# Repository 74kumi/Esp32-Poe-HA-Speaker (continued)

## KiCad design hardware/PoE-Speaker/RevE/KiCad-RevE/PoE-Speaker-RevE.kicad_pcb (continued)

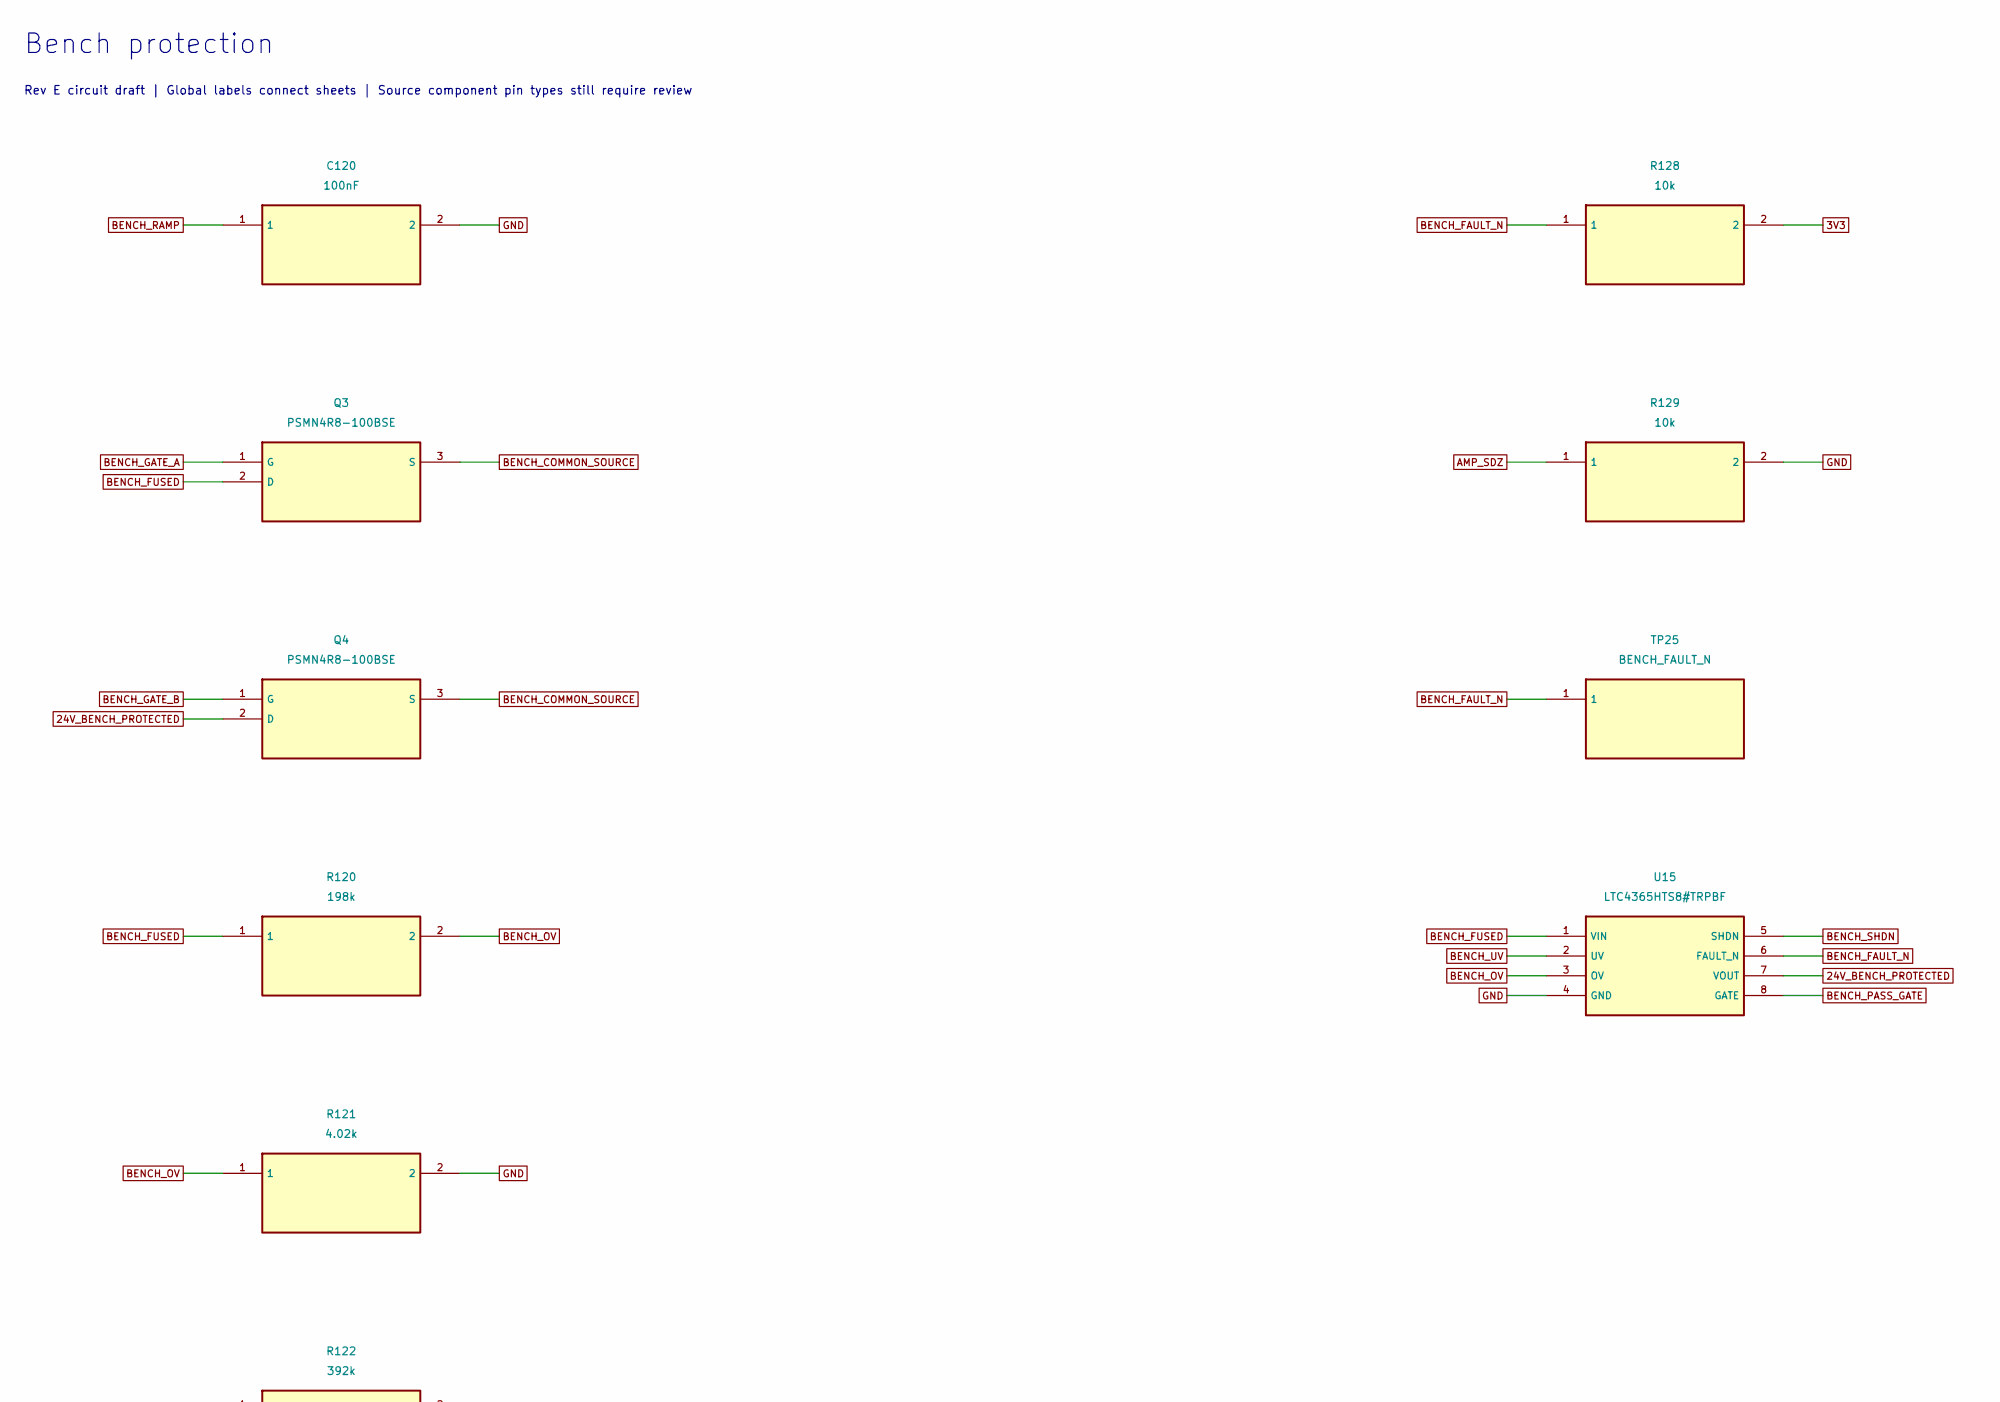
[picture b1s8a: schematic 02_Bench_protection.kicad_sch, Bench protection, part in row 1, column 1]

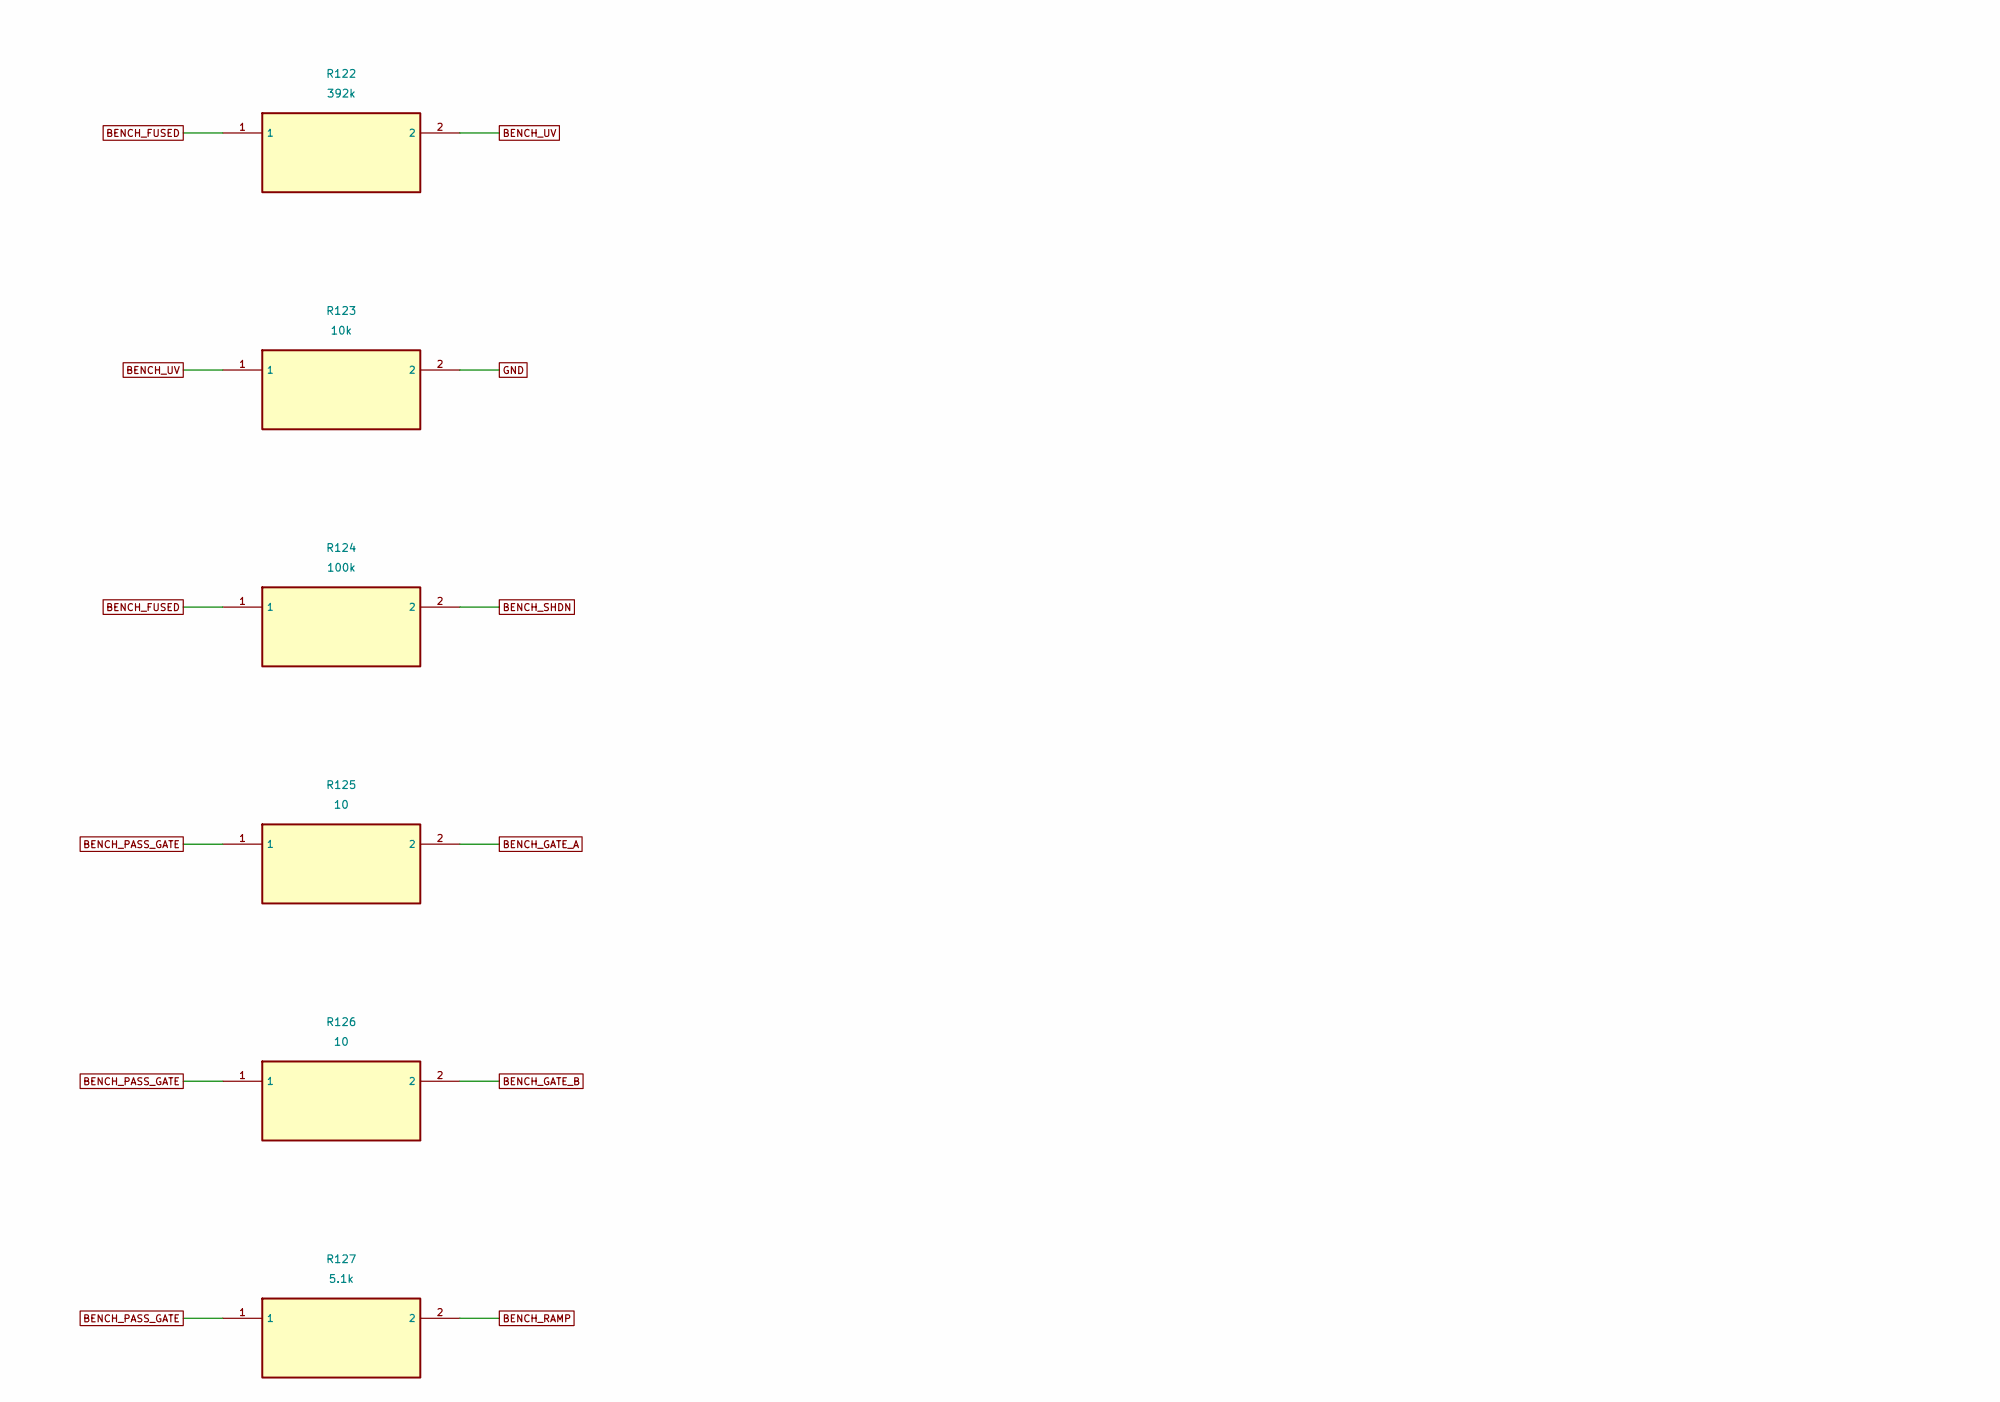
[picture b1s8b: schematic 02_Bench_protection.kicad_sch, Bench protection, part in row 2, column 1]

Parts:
C120: 100nF; C_1210_3225Metric; Voltage Rating 100 V; Tolerance 5%; Manufacturer Part Number C1210C104J1GACTU
Q3: PSMN4R8-100BSE; Q3_RevB; Manufacturer Part Number PSMN4R8-100BSE
Q4: PSMN4R8-100BSE; Q4_RevB; Manufacturer Part Number PSMN4R8-100BSE
R120: 198k; R120_RevB; Tolerance 0.1%; Power rating 0.125 W conservative; Manufacturer Part Number TNPW0805198KBYEA
R121: 4.02k; R121_RevB; Tolerance 0.1%; Power rating 0.125 W conservative; Manufacturer Part Number TNPW08054K02BYEA
R122: 392k; R122_RevB; Tolerance 1%; Power rating 0.125 W conservative; Manufacturer Part Number TNPW0805392KFHEA
R123: 10k; R123_RevB; Tolerance 1%; Power rating 0.125 W conservative; Manufacturer Part Number TNPW080510K0FHEA
R124: 100k; R124_RevB; Tolerance 1%; Power rating 0.125 W conservative; Manufacturer Part Number TNPW0805100KFHEA
R125: 10; R125_RevB; Tolerance 1%; Power rating 0.125 W conservative; Manufacturer Part Number TNPW080510R0FHEA
R126: 10; R126_RevB; Tolerance 1%; Power rating 0.125 W conservative; Manufacturer Part Number TNPW080510R0FHEA
R127: 5.1k; R127_RevB; Tolerance 1%; Power rating 0.125 W conservative; Manufacturer Part Number TNPW08055K10FHEA
R128: 10k; R128_RevB; Tolerance 1%; Power rating 0.125 W conservative; Manufacturer Part Number TNPW080510K0FHEA
R129: 10k; R129_RevB; Tolerance 1%; Power rating 0.125 W conservative; Manufacturer Part Number TNPW080510K0FHEA
TP25: BENCH_FAULT_N; TP25_RevB; Manufacturer Part Number BENCH_FAULT_N
U15: LTC4365HTS8#TRPBF; U15_RevB; Manufacturer Part Number LTC4365HTS8#TRPBF

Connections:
3V3: R128.2; also elsewhere on the board
24V_BENCH_PROTECTED: Q4.2 (D), U15.7 (VOUT); also elsewhere on the board
AMP_SDZ: R129.1; also elsewhere on the board
BENCH_COMMON_SOURCE: Q3.3 (S), Q4.3 (S)
BENCH_FAULT_N: R128.1, TP25.1, U15.6 (FAULT_N)
BENCH_FUSED: Q3.2 (D), R120.1, R122.1, R124.1, U15.1 (VIN); also elsewhere on the board
BENCH_GATE_A: Q3.1 (G), R125.2
BENCH_GATE_B: Q4.1 (G), R126.2
BENCH_OV: R120.2, R121.1, U15.3 (OV)
BENCH_PASS_GATE: R125.1, R126.1, R127.1, U15.8 (GATE)
BENCH_RAMP: C120.1, R127.2
BENCH_SHDN: R124.2, U15.5 (SHDN)
BENCH_UV: R122.2, R123.1, U15.2 (UV)
GND: C120.2, R121.2, R123.2, R129.2, U15.4 (GND); also elsewhere on the board

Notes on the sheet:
Bench protection
Rev E circuit draft | Global labels connect sheets | Source component pin types still require review

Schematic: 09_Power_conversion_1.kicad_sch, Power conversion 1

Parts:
C3: 1000uF; C3_RevB; Voltage Rating 35V; Manufacturer Part Number EEUFR1V102
C4: 1000uF; C4_RevB; Voltage Rating 35V; Manufacturer Part Number EEUFR1V102
C40: 10uF; C40_RevB; Voltage Rating 50 V; Tolerance 10%; Manufacturer Part Number C1210C106K5RACTU
C41: 220nF; C41_RevB; Voltage Rating 50 V; Tolerance 10%; Manufacturer Part Number C0603C224K5RACTU
C42: 100nF; C42_RevB; Voltage Rating 50 V; Tolerance 10%; Manufacturer Part Number C0603C104K5RACTU
C43: 1uF; C43_RevB; Voltage Rating 16 V; Tolerance 10%; Manufacturer Part Number C0603C105K4RACTU
C44: 22uF; C44_RevB; Voltage Rating 25 V; Tolerance 10%; Manufacturer Part Number C1210C226K3RACTU
C45: 22uF; C45_RevB; Voltage Rating 25 V; Tolerance 10%; Manufacturer Part Number C1210C226K3RACTU
C46: 22uF; C46_RevB; Voltage Rating 25 V; Tolerance 10%; Manufacturer Part Number C1210C226K3RACTU
C47: 22uF; C47_RevB; Voltage Rating 25 V; Tolerance 10%; Manufacturer Part Number C1210C226K3RACTU
C48: 10uF; C48_RevB; Voltage Rating 16 V; Tolerance 10%; Manufacturer Part Number GRM21BR61C106KE15L
C49: 22uF; C49_RevB; Voltage Rating 16 V; Tolerance 20%; Manufacturer Part Number GRM21BR61C226ME44L
C50: 47uF; C50_RevB; Voltage Rating 16 V; Tolerance 10%; Manufacturer Part Number GRM32ER61C476KE15L
C53: 3.3nF; C53_RevB; Voltage Rating 50 V; Tolerance 5%; Manufacturer Part Number C0603C332J5GACTU
D11: SMBJ26CA; D11_RevB; Manufacturer Part Number SMBJ26CA
F1: 24T 3.15A250V; F1_RevB; Manufacturer Part Number 24T 3.15A250V; LCSC Part Number C2905508
J2: MX2EDGR-5.08-02P-GN01-Cu-A; J2_RevB; Manufacturer Part Number MX2EDGR-5.08-02P-GN01-Cu-A; LCSC Part Number C5187973
L3: 8.2uH; L3_RevB; Current Rating 4A; Part Type Inductor
L4: 2.2uH; L4_RevB; Current Rating 4A; Part Type Inductor
Q1: DMNH6012LK3-13; Q1_RevB; Manufacturer Part Number DMNH6012LK3-13
Q2: DMNH6012LK3-13; Q2_RevB; Manufacturer Part Number DMNH6012LK3-13

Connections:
3V3: C49.1, C50.1, L4.2; also elsewhere on the board
5V: C44.1, C45.1, C46.1, C47.1, C48.1, L3.2; also elsewhere on the board
24V_AMP: C3.1, C4.1, C40.1, C41.1; also elsewhere on the board
24V_BENCH_PROTECTED: Q2.3 (S); also elsewhere on the board
24V_BENCH_RAW: F1.1, J2.1; also elsewhere on the board
24V_OR: Q1.2 (D), Q2.2 (D); also elsewhere on the board
24V_POE: Q1.3 (S); also elsewhere on the board
BENCH_FUSED: D11.1 (K), F1.2; also elsewhere on the board
BENCH_OR_GATE: Q2.1 (G); also elsewhere on the board
BUCK3V3_SS: C53.1; also elsewhere on the board
BUCK3V3_SW: L4.1; also elsewhere on the board
BUCK5_BOOT: C42.1; also elsewhere on the board
BUCK5_SW: C42.2, L3.1; also elsewhere on the board
BUCK5_VCC: C43.1; also elsewhere on the board
GND: C3.2, C4.2, C40.2, C41.2, C43.2, C44.2, C45.2, C46.2, C47.2, C48.2, C49.2, C50.2, C53.2, D11.2 (A), J2.2; also elsewhere on the board
POE_OR_GATE: Q1.1 (G); also elsewhere on the board

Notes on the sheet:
Power conversion 1
Rev E circuit draft | Global labels connect sheets | Source component pin types still require review

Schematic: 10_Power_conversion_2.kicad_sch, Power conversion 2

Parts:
R23: 100kΩ; R23_RevB; Tolerance 1%; Power rating 0.10 W conservative; Part Type Resistor
R24: 24.9kΩ; R24_RevB; Tolerance 1%; Power rating 0.10 W conservative; Part Type Resistor
R35: 100kΩ; R35_RevB; Tolerance 1%; Power rating 0.10 W conservative; Part Type Resistor
R36: 100kΩ; R36_RevB; Tolerance 1%; Power rating 0.10 W conservative; Part Type Resistor
U6: LMR33630AQRNXRQ1; U6_RevB; Manufacturer Part Number LMR33630AQRNXRQ1
U7: TPS62132RGTR; U7_RevB; Part Type Integrated Circuit
U9: LM5050-2; U9_RevB; Manufacturer Part Number LM5050MK-2/NOPB
U10: LM5050-2; U10_RevB; Manufacturer Part Number LM5050MK-2/NOPB

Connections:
3V3: R36.2, U7.7 (FSW), U7.14 (VOS); also elsewhere on the board
3V3_PG: R36.1, U7.4 (PG); also elsewhere on the board
5V: R23.1, R35.2, U7.10 (AVIN), U7.11 (PVIN_1), U7.12 (PVIN_2), U7.13 (EN); also elsewhere on the board
5V_PG: R35.1, U6.8 (PG); also elsewhere on the board
24V_AMP: U6.2 (VIN), U6.9 (EN), U6.10 (VIN); also elsewhere on the board
24V_BENCH_PROTECTED: U10.4 (IN); also elsewhere on the board
24V_OR: U9.6 (OUT), U10.6 (OUT); also elsewhere on the board
24V_POE: U9.4 (IN); also elsewhere on the board
BENCH_OR_GATE: U10.5 (GATE); also elsewhere on the board
BUCK3V3_SS: U7.9 (SS/TR); also elsewhere on the board
BUCK3V3_SW: U7.1 (SW_1), U7.2 (SW_2), U7.3 (SW_3); also elsewhere on the board
BUCK5_BOOT: U6.4 (BST); also elsewhere on the board
BUCK5_FB: R23.2, R24.1, U6.7 (FB)
BUCK5_SW: U6.3 (NC), U6.12 (SW); also elsewhere on the board
BUCK5_VCC: U6.5 (VCC); also elsewhere on the board
GND: R24.2, U6.1 (PGND), U6.6 (AGND), U6.11 (PGND), U7.5 (FB), U7.6 (AGND), U7.8 (DEF), U7.15 (PGND_1), U7.16 (PGND_2), U7.17 (EP), U9.2 (GND), U9.3 (OFF), U10.2 (GND), U10.3 (OFF); also elsewhere on the board
POE_OR_GATE: U9.5 (GATE); also elsewhere on the board

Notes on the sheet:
Rev E circuit draft | Global labels connect sheets | Source component pin types still require review
Power conversion 2

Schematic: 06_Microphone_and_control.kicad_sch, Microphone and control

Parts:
C55: 100nF; C55_RevB; Voltage Rating 50 V; Tolerance 10%; Manufacturer Part Number C0603C104K5RACTU
C56: 100nF; C56_RevB; Voltage Rating 50 V; Tolerance 10%; Manufacturer Part Number C0603C104K5RACTU
C57: 100nF; C57_RevB; Voltage Rating 50 V; Tolerance 10%; Manufacturer Part Number C0603C104K5RACTU
J4: Pin Header 02x07 2.54mm Vertical; J4_RevB; Manufacturer Part Number TSW-107-07-G-D
J6: Pin Header 01x06 2.54mm Vertical; J6_RevB; Part Type Connector
R28: 33Ω; R28_RevB; Tolerance 1%; Power rating 0.10 W conservative; Part Type Resistor
R29: 33Ω; R29_RevB; Tolerance 1%; Power rating 0.10 W conservative; Part Type Resistor
R30: 33Ω; R30_RevB; Tolerance 1%; Power rating 0.10 W conservative; Part Type Resistor
R31: 33Ω; R31_RevB; Tolerance 1%; Power rating 0.10 W conservative; Part Type Resistor
R32: 33Ω; R32_RevB; Tolerance 1%; Power rating 0.10 W conservative; Part Type Resistor
R33: 4.7kΩ; R33_RevB; Tolerance 1%; Power rating 0.10 W conservative; Part Type Resistor
R34: 4.7kΩ; R34_RevB; Tolerance 1%; Power rating 0.10 W conservative; Part Type Resistor
R38: 10kΩ; R38_RevB; Tolerance 1%; Power rating 0.10 W conservative; Part Type Resistor
U11: PCAL6416APW; U11_RevB; Manufacturer Part Number PCAL6416APW

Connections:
3V3: C55.1, C56.1, C57.1, J4.1, J6.1, R33.1, R34.1, R38.1, U11.2 (VDD_I2C), U11.24 (VDD_P); also elsewhere on the board
3V3_PG: U11.14 (P1_1); also elsewhere on the board
5V_PG: U11.13 (P1_0); also elsewhere on the board
AMP_ENABLE_CMD: U11.4 (P0_0); also elsewhere on the board
AMP_FAULTZ: U11.8 (P0_4); also elsewhere on the board
AMP_MUTE: U11.5 (P0_1); also elsewhere on the board
DAC_XSMT: U11.6 (P0_2); also elsewhere on the board
EXP_GPIO0: J6.5, U11.15 (P1_2)
EXP_GPIO1: J6.6, U11.16 (P1_3)
GND: C55.2, C56.2, C57.2, J4.2, J4.4, J4.6, J4.8, J4.10, J6.2, U11.12 (VSS), U11.21 (ADDR); also elsewhere on the board
I2C_SCL: J4.13, J6.4, R34.2, U11.22 (SCL); also elsewhere on the board
I2C_SDA: J4.12, J6.3, R33.2, U11.23 (SDA); also elsewhere on the board
IOX_INT_N: U11.1 (~INT); also elsewhere on the board
IOX_nRESET: R38.2, U11.3 (~RESET); also elsewhere on the board
PDM_CLK: J4.3, R28.2; also elsewhere on the board
PDM_CLK_MCU: R28.1; also elsewhere on the board
PDM_DATA0: R29.2; also elsewhere on the board
PDM_DATA0_CONN: J4.5, R29.1
PDM_DATA1: R30.2; also elsewhere on the board
PDM_DATA1_CONN: J4.7, R30.1
PDM_DATA2: R31.2; also elsewhere on the board
PDM_DATA2_CONN: J4.9, R31.1
PDM_DATA3: R32.2; also elsewhere on the board
PDM_DATA3_CONN: J4.11, R32.1
PHY_nRESET: U11.7 (P0_3); also elsewhere on the board
POE_AT_DET: U11.9 (P0_5); also elsewhere on the board
POE_BT3_DET: U11.10 (P0_6); also elsewhere on the board
POE_BT4_DET: U11.11 (P0_7); also elsewhere on the board
RING_GPIO_SPARE: J4.14; also elsewhere on the board
STATUS_LED_K: U11.17 (P1_4); also elsewhere on the board

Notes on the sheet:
Microphone and control
Rev E circuit draft | Global labels connect sheets | Source component pin types still require review

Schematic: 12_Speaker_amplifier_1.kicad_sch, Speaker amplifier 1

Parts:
C5: 100uF; C5_RevB; Voltage Rating 50V; Manufacturer Part Number EEUFR1H101
C6: 100uF; C6_RevB; Voltage Rating 50V; Manufacturer Part Number EEUFR1H101
C7: 220nF; C7_RevB; Voltage Rating 50 V; Tolerance 10%; Manufacturer Part Number C0603C224K5RACTU
C8: 220nF; C8_RevB; Voltage Rating 50 V; Tolerance 10%; Manufacturer Part Number C0603C224K5RACTU
C9: 220nF; C9_RevB; Voltage Rating 50 V; Tolerance 10%; Manufacturer Part Number C0603C224K5RACTU
C10: 220nF; C10_RevB; Voltage Rating 50 V; Tolerance 10%; Manufacturer Part Number C0603C224K5RACTU
C11: 1uF; C11_RevB; Voltage Rating 16 V; Tolerance 10%; Manufacturer Part Number C0603C105K4RACTU
C12: 1uF; C12_RevB; Voltage Rating 100 V; Tolerance 10%; Manufacturer Part Number C1210C105K1RACTU
C13: 1uF; C13_RevB; Voltage Rating 100 V; Tolerance 10%; Manufacturer Part Number C1210C105K1RACTU
C14: 1uF; C14_RevB; Voltage Rating 100 V; Tolerance 10%; Manufacturer Part Number C1210C105K1RACTU
C15: 1uF; C15_RevB; Voltage Rating 100 V; Tolerance 10%; Manufacturer Part Number C1210C105K1RACTU
C16: 1uF; C16_RevB; Voltage Rating 100 V; Tolerance 10%; Manufacturer Part Number C1210C105K1RACTU
C17: 2.2uF; C17_RevB; Voltage Rating 25 V; Tolerance 10%; Manufacturer Part Number C0805C225K3RACTU
C18: 2.2uF; C18_RevB; Voltage Rating 25 V; Tolerance 10%; Manufacturer Part Number C0805C225K3RACTU
C58: 1uF; C58_RevB; Voltage Rating 16 V; Tolerance 10%; Manufacturer Part Number C0603C105K4RACTU
J3: MX2EDGR-5.08-02P-GN01-Cu-A; J3_RevB; Manufacturer Part Number MX2EDGR-5.08-02P-GN01-Cu-A; LCSC Part Number C5187973
L1: 10uH; L1_RevB; Current Rating 5A; Part Type Inductor
L2: 10uH; L2_RevB; Current Rating 5A; Part Type Inductor
R14: 5.6kΩ; R14_RevB; Tolerance 1%; Power rating 0.10 W conservative; Part Type Resistor
R15: 82kΩ; R15_RevB; Power rating 0.10 W conservative; Tolerance 1%; Part Type Resistor
R16: 51kΩ; R16_RevB; Power rating 0.10 W conservative; Tolerance 1%; Part Type Resistor

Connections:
24V_AMP: C5.1, C6.1, C12.1, C13.1, C14.1, C15.1; also elsewhere on the board
AMP_BSNL: C7.1; also elsewhere on the board
AMP_BSNR: C9.1; also elsewhere on the board
AMP_BSPL: C8.1; also elsewhere on the board
AMP_BSPR: C10.1; also elsewhere on the board
AMP_GAIN: R14.1; also elsewhere on the board
AMP_GVDD: C11.1, R15.1; also elsewhere on the board
AMP_IN_N: C18.2; also elsewhere on the board
AMP_IN_P: C17.2; also elsewhere on the board
AMP_PLIMIT: C58.1, R15.2, R16.1; also elsewhere on the board
AMP_SW_NEG: C7.2, C8.2, L2.1; also elsewhere on the board
AMP_SW_POS: C9.2, C10.2, L1.1; also elsewhere on the board
DAC_OUT_FILTERED: C17.1; also elsewhere on the board
GND: C5.2, C6.2, C11.2, C12.2, C13.2, C14.2, C15.2, C18.1, C58.2, R14.2, R16.2; also elsewhere on the board
SPK_NEG: C16.2, J3.2, L2.2
SPK_POS: C16.1, J3.1, L1.2

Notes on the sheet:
Speaker amplifier 1
Rev E circuit draft | Global labels connect sheets | Source component pin types still require review

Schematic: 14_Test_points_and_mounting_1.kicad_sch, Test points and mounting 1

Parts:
H1: MountingHole; H1_RevB; Manufacturer Part Number MountingHole
H2: MountingHole; H2_RevB; Manufacturer Part Number MountingHole
H3: MountingHole; H3_RevB; Manufacturer Part Number MountingHole
H4: MountingHole; H4_RevB; Manufacturer Part Number MountingHole
TP1: Generic Testpoint; TP1_RevB; Part Type Test Point
TP2: Generic Testpoint; TP2_RevB; Part Type Test Point
TP3: Generic Testpoint; TP3_RevB; Part Type Test Point
TP4: Generic Testpoint; TP4_RevB; Part Type Test Point
TP5: Generic Testpoint; TP5_RevB; Part Type Test Point
TP6: Generic Testpoint; TP6_RevB; Part Type Test Point
TP7: Generic Testpoint; TP7_RevB; Part Type Test Point
TP8: Generic Testpoint; TP8_RevB; Part Type Test Point
TP9: Generic Testpoint; TP9_RevB; Part Type Test Point
TP10: Generic Testpoint; TP10_RevB; Part Type Test Point
TP11: Generic Testpoint; TP11_RevB; Part Type Test Point
TP12: Generic Testpoint; TP12_RevB; Part Type Test Point
TP13: Generic Testpoint; TP13_RevB; Part Type Test Point
TP14: Generic Testpoint; TP14_RevB; Part Type Test Point
TP15: Generic Testpoint; TP15_RevB; Part Type Test Point
TP16: Generic Testpoint; TP16_RevB; Part Type Test Point
TP17: Generic Testpoint; TP17_RevB; Part Type Test Point

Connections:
3V3: TP5.1; also elsewhere on the board
5V: TP4.1; also elsewhere on the board
24V_AMP: TP3.1; also elsewhere on the board
AMP_FAULTZ: TP14.1; also elsewhere on the board
AMP_SDZ: TP13.1; also elsewhere on the board
ETH_SPI_MOSI: TP11.1; also elsewhere on the board
ETH_SPI_SCLK: TP10.1; also elsewhere on the board
GND: TP6.1; also elsewhere on the board
I2S_BCLK: TP7.1; also elsewhere on the board
I2S_DATA: TP9.1; also elsewhere on the board
I2S_LRCLK: TP8.1; also elsewhere on the board
PDM_CLK: TP15.1; also elsewhere on the board
PDM_DATA0: TP16.1; also elsewhere on the board
PDM_DATA1: TP17.1; also elsewhere on the board
PHY_nRESET: TP12.1; also elsewhere on the board
POE_RECT_NEG: TP2.1; also elsewhere on the board
POE_RECT_POS: TP1.1; also elsewhere on the board

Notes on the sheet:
Rev E circuit draft | Global labels connect sheets | Source component pin types still require review
Test points and mounting 1

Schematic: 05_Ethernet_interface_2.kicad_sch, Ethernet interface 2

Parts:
LED3: SML-D13FWT86C; LED3_RevB; Manufacturer Part Number SML-D13FWT86C
R25: 1kΩ; R25_RevB; Tolerance 1%; Power rating 0.10 W conservative; Part Type Resistor
R26: 1kΩ; R26_RevB; Tolerance 1%; Power rating 0.10 W conservative; Part Type Resistor
R27: 1kΩ; R27_RevB; Tolerance 1%; Power rating 0.10 W conservative; Part Type Resistor
R100: 12.4k; R100_RevB; Tolerance 1%; Power rating 0.10 W conservative; Manufacturer Part Number TNPW060312K4FHEA
R101: 49.9; R101_RevB; Tolerance 1%; Power rating 0.10 W conservative; Manufacturer Part Number TNPW060349R9FHEA
R102: 49.9; R102_RevB; Tolerance 1%; Power rating 0.10 W conservative; Manufacturer Part Number TNPW060349R9FHEA
R103: 10; R103_RevB; Tolerance 1%; Power rating 0.10 W conservative; Manufacturer Part Number TNPW060310R0FHEA
R104: 49.9; R104_RevB; Tolerance 1%; Power rating 0.10 W conservative; Manufacturer Part Number TNPW060349R9FHEA
R105: 49.9; R105_RevB; Tolerance 1%; Power rating 0.10 W conservative; Manufacturer Part Number TNPW060349R9FHEA
R106: 10k; R106_RevB; Tolerance 1%; Power rating 0.10 W conservative; Manufacturer Part Number TNPW060310K0FHEA
R107: 10k; R107_RevB; Tolerance 1%; Power rating 0.10 W conservative; Manufacturer Part Number TNPW060310K0FHEA
R108: 33; R108_RevB; Tolerance 1%; Power rating 0.10 W conservative; Manufacturer Part Number TNPW060333R0FHEA
R109: 33; R109_RevB; Tolerance 1%; Power rating 0.10 W conservative; Manufacturer Part Number TNPW060333R0FHEA
U3: W5500; U3_RevB; Manufacturer Part Number W5500
X2: 25MHz; X2_RevB; Manufacturer Part Number ASE-25.000MHZ-LC-T

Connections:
3V3: R25.2, R27.2, R106.1, R107.1, U3.28 (VDD), U3.43 (PMODE2), U3.44 (PMODE1), U3.45 (PMODE0), X2.1, X2.4; also elsewhere on the board
ETH_1V2: U3.22 (1V2O); also elsewhere on the board
ETH_3V3A: R101.2, R102.2, R103.1, U3.4 (AVDD), U3.8 (AVDD), U3.11 (AVDD), U3.15 (AVDD), U3.17 (AVDD), U3.21 (AVDD); also elsewhere on the board
ETH_25MHZ: U3.30 (XI/CLKIN), X2.3
ETH_EXRES: R100.1, U3.10 (EXRES1)
ETH_INT_N: U3.36 (~INT); also elsewhere on the board
ETH_RX_N: R105.1, U3.5 (RXN); also elsewhere on the board
ETH_RX_P: R104.1, U3.6 (RXP); also elsewhere on the board
ETH_RX_TERM: R104.2, R105.2; also elsewhere on the board
ETH_SPI_CS_N: R107.2, U3.32 (~SCS); also elsewhere on the board
ETH_SPI_MISO: U3.34 (MISO); also elsewhere on the board
ETH_SPI_MOSI: R109.2, U3.35 (MOSI); also elsewhere on the board
ETH_SPI_MOSI_MCU: R109.1; also elsewhere on the board
ETH_SPI_SCLK: R108.2, U3.33 (SCLK); also elsewhere on the board
ETH_SPI_SCLK_MCU: R108.1; also elsewhere on the board
ETH_TOCAP: U3.20 (TOCAP); also elsewhere on the board
ETH_TX_CT: R103.2; also elsewhere on the board
ETH_TX_N: R102.1, U3.1 (TXN); also elsewhere on the board
ETH_TX_P: R101.1, U3.2 (TXP); also elsewhere on the board
GND: R100.2, U3.3 (AGND), U3.9 (AGND), U3.14 (AGND), U3.16 (AGND), U3.19 (AGND), U3.23 (RSVD), U3.29 (GND), U3.48 (AGND), X2.2; also elsewhere on the board
PHY_LED_A: R25.1; also elsewhere on the board
PHY_LINK_LED: U3.25 (LINKLED); also elsewhere on the board
PHY_SPEED_LED: R26.1, U3.24 (SPDLED)
PHY_SPEED_LED_A: R26.2; also elsewhere on the board
PHY_nRESET: R106.2, U3.37 (~RST); also elsewhere on the board
STATUS_LED_A: LED3.2, R27.1
STATUS_LED_K: LED3.1; also elsewhere on the board

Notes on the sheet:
Rev E circuit draft | Global labels connect sheets | Source component pin types still require review
Ethernet interface 2

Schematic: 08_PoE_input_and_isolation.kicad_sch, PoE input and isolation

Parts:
C1: 1000uF; C1_RevB; Voltage Rating 25V; Manufacturer Part Number EEUFR1E102
C2: 1000uF; C2_RevB; Voltage Rating 25V; Manufacturer Part Number EEUFR1E102
D2: SMAJ58A-TR; D2_RevB; Manufacturer Part Number SMAJ58A-TR; JLCPCB Part Class Extended Part
D3: B5100C; D3_RevB; Forward Voltage 0.85 V max at 5 A; Reverse Voltage 100; Manufacturer Part Number B5100C
D4: B5100C; D4_RevB; Forward Voltage 0.85 V max at 5 A; Reverse Voltage 100; Manufacturer Part Number B5100C
D5: B5100C; D5_RevB; Forward Voltage 0.85 V max at 5 A; Reverse Voltage 100; Manufacturer Part Number B5100C
D6: B5100C; D6_RevB; Forward Voltage 0.85 V max at 5 A; Reverse Voltage 100; Manufacturer Part Number B5100C
D7: B5100C; D7_RevB; Forward Voltage 0.85 V max at 5 A; Reverse Voltage 100; Manufacturer Part Number B5100C
D8: B5100C; D8_RevB; Forward Voltage 0.85 V max at 5 A; Reverse Voltage 100; Manufacturer Part Number B5100C
D9: B5100C; D9_RevB; Forward Voltage 0.85 V max at 5 A; Reverse Voltage 100; Manufacturer Part Number B5100C
D10: B5100C; D10_RevB; Forward Voltage 0.85 V max at 5 A; Reverse Voltage 100; Manufacturer Part Number B5100C
R3: 27kΩ; R3_RevB; Power rating 0.25 W conservative; Tolerance 1%; Part Type Resistor
R4: 27kΩ; R4_RevB; Power rating 0.25 W conservative; Tolerance 1%; Part Type Resistor
R5: 27kΩ; R5_RevB; Power rating 0.25 W conservative; Tolerance 1%; Part Type Resistor
R6: 10kΩ; R6_RevB; Tolerance 1%; Power rating 0.10 W conservative; Part Type Resistor
R7: 10kΩ; R7_RevB; Tolerance 1%; Power rating 0.10 W conservative; Part Type Resistor
R8: 10kΩ; R8_RevB; Tolerance 1%; Power rating 0.10 W conservative; Part Type Resistor
U1: Ag5800; U1_RevB; Part Type Integrated Circuits
U12: PC817X2NSZ9F; U12_RevB; Part Type Optocouplers - Phototransistor Output; LCSC Part Number C390734
U13: PC817X2NSZ9F; U13_RevB; Part Type Optocouplers - Phototransistor Output; LCSC Part Number C390734
U14: PC817X2NSZ9F; U14_RevB; Part Type Optocouplers - Phototransistor Output; LCSC Part Number C390734

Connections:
3V3: R6.2, R7.2, R8.2; also elsewhere on the board
24V_POE: C2.1, U1.9 (VOUT2_1), U1.10 (VOUT2_2); also elsewhere on the board
AT_DET_PRIMARY: U1.3 (AT-DET), U12.2 (Cathode)
AT_LED_A: R3.2, U12.1 (Anode)
BT3_DET_PRIMARY: U1.4 (TYP3-DET), U13.2 (Cathode)
BT3_LED_A: R4.2, U13.1 (Anode)
BT4_DET_PRIMARY: U1.5 (TYP4-DET), U14.2 (Cathode)
BT4_LED_A: R5.2, U14.1 (Anode)
GND: C1.2, U1.15 (0V1_1), U1.16 (0V1_2), U12.3 (Emitter), U13.3 (Emitter), U14.3 (Emitter); also elsewhere on the board
POE_12V_MID: C1.1, C2.2, U1.11 (0V2_1), U1.12 (0V2_2), U1.13 (VOUT1_1), U1.14 (VOUT1_2)
POE_AT_DET: R6.1, U12.4 (Collector); also elsewhere on the board
POE_BT3_DET: R7.1, U13.4 (Collector); also elsewhere on the board
POE_BT4_DET: R8.1, U14.4 (Collector); also elsewhere on the board
POE_MODE_A_AC1: D3.1 (A), D5.2 (K); also elsewhere on the board
POE_MODE_A_AC2: D4.1 (A), D6.2 (K); also elsewhere on the board
POE_MODE_B_AC1: D7.1 (A), D9.2 (K); also elsewhere on the board
POE_MODE_B_AC2: D8.1 (A), D10.2 (K); also elsewhere on the board
POE_RECT_NEG: D2.2 (A), D5.1 (A), D6.1 (A), D9.1 (A), D10.1 (A), U1.7 (VIN-); also elsewhere on the board
POE_RECT_POS: D2.1 (K), D3.2 (K), D4.2 (K), D7.2 (K), D8.2 (K), R3.1, R4.1, R5.1, U1.8 (VIN+); also elsewhere on the board

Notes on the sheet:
PoE input and isolation
Rev E circuit draft | Global labels connect sheets | Source component pin types still require review

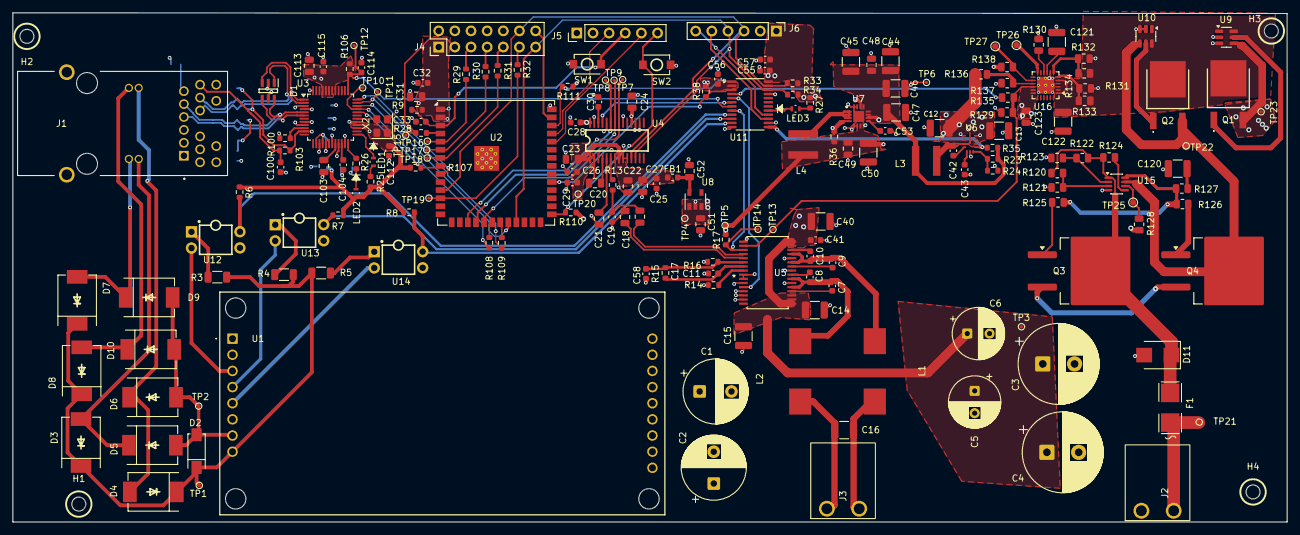
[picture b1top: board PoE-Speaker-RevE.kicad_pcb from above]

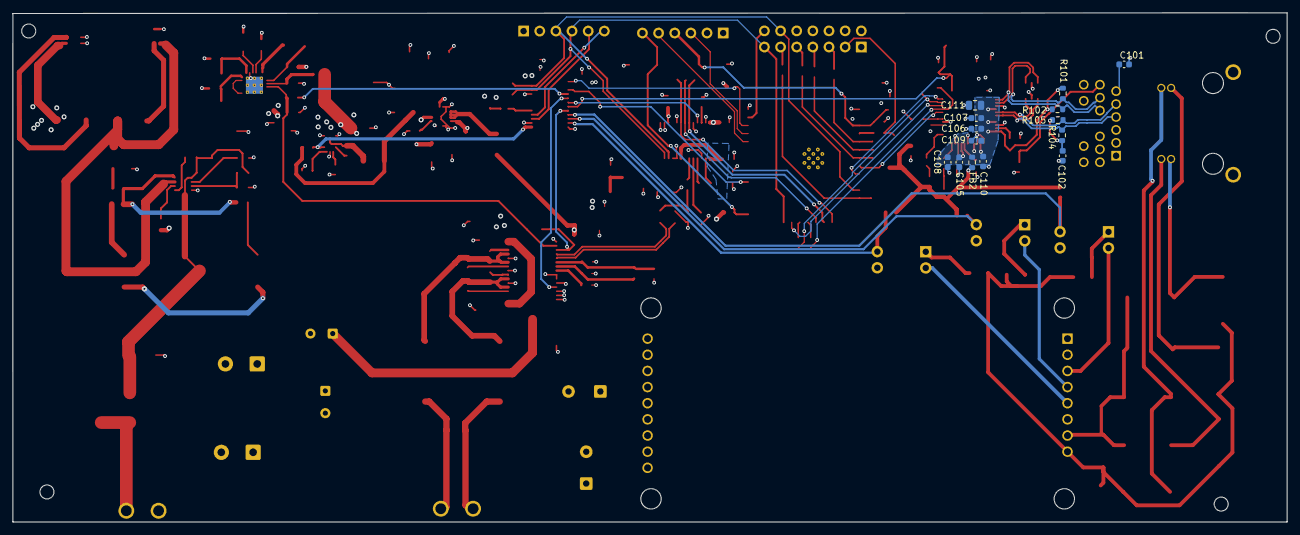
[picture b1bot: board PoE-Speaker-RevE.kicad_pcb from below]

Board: 4 copper layers, 200.4 x 80.1 mm, 209 parts (14 on the bottom side), 127 nets.
